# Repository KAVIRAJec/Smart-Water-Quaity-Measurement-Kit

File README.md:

# 🌐 Smart Water Quality Monitoring System Repository

Welcome to the repository for our Smart Water Quality Monitoring System! 🚰

## Project Overview

This repository hosts the code and documentation for an innovative smart water quality monitoring system. Our goal is to provide real-time insights into the quality of drinking water through a seamlessly integrated system.

## Key Components

- **Double-layer PCB Design:** Schematics and layouts meticulously crafted for enhanced performance.
  
- **3D-Printed Sensor Housings:** Custom-designed sensor housings using advanced 3D printing techniques.
  
- **Industrial Sensors:** Integration of industrial-grade pH, ORP, TDS, and turbidity sensors for accurate readings.

- **Raspberry Pi 4:** The core of our system, handling data processing and communication tasks efficiently.

- **Nextion HMI Touch Display:** An interactive touch display for real-time data visualization.

- **Mobile Application:** Developed using React Native, Node.js Express, and a robust database for accessible monitoring.

## Contributions

- **PCB Design:** Developed intricate double-layer PCB schematics and layouts.
  
- **3D Design and Printing:** Created and printed custom sensor housings for optimal functionality.
  
- **Hardware Integration:** Seamlessly integrated various hardware components and peripherals.
  
- **Raspberry Pi Programming:** Wrote the necessary code for Raspberry Pi, ensuring smooth data processing and communication.
  
- **Mobile Application Development:** Utilized React Native, Node.js Express, and database technologies for a user-friendly mobile application.

## Skills and Technologies Showcased

- **PCB Design:** Proficiency in crafting intricate PCB schematics and layouts.
  
- **3D Design and Printing:** Skillful creation and printing of custom 3D sensor housings.
  
- **Hardware Integration:** Expertise in integrating diverse hardware components seamlessly.
  
- **Raspberry Pi Programming:** Coding proficiency for efficient data processing on Raspberry Pi.
  
- **React Native:** Development of a mobile application for versatile accessibility.
  
- **Node.js Express:** Utilized for the backend of the mobile application.
  
- **Database Technologies:** Implemented a robust database for storing and managing data.

## License

This project is licensed under the MIT License
## Collaboration

This project is open to all collaborators! Feel free to contribute by forking the repository and creating pull requests.

## Documentation

Check the folders for comprehensive documentation related to the Smart Water Quality Monitoring System.

Feel free to explore the codebase and documentation to understand the inner workings of our Smart Water Quality Monitoring System! 💻🚀

#WaterQuality #SmartMonitoring #OpenSource #TechInnovation

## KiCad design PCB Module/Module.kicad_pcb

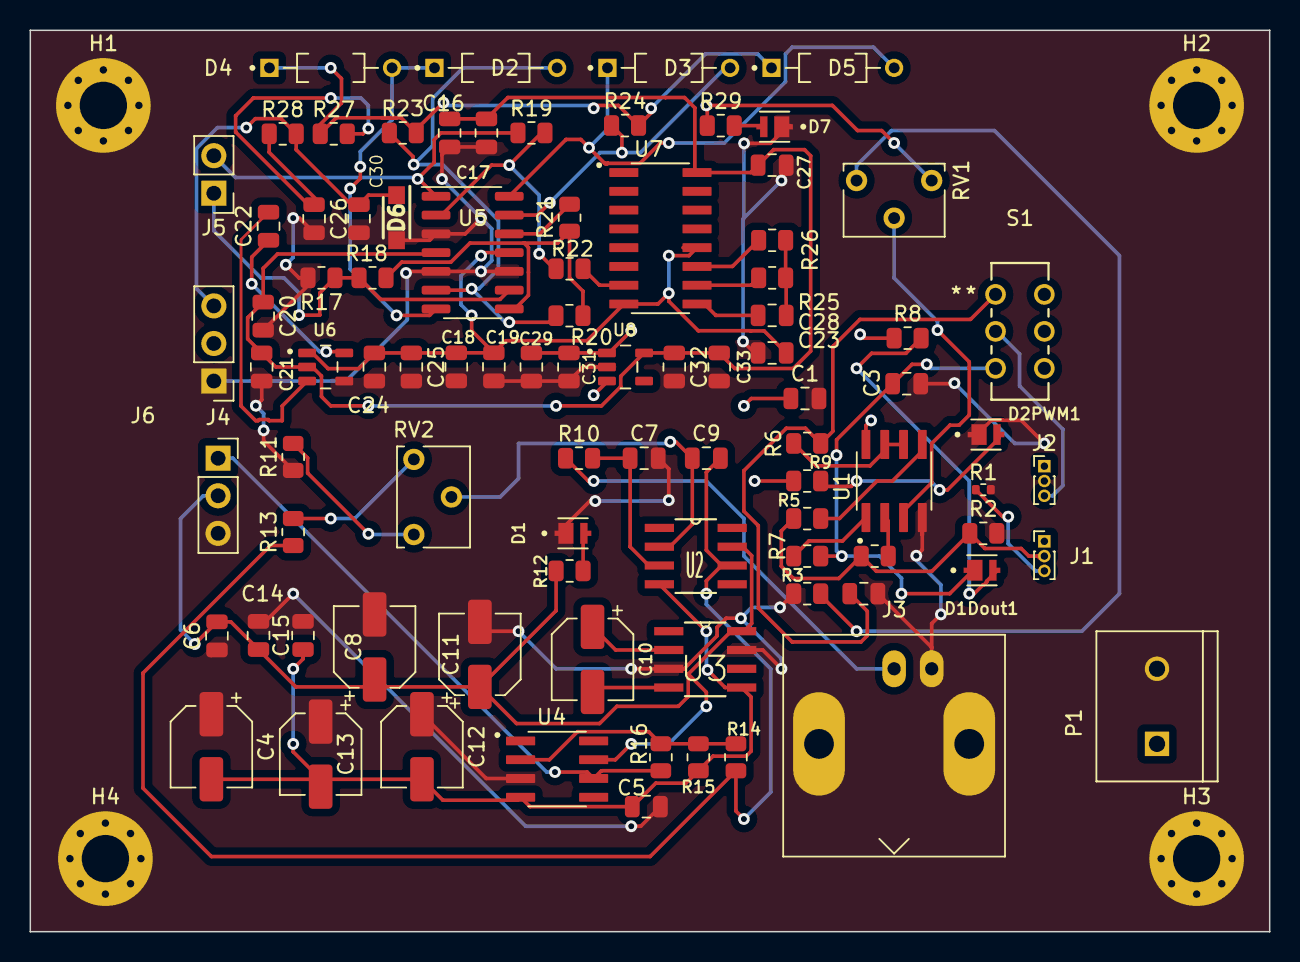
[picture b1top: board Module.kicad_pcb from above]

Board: 2 copper layers, 83.8 x 61.0 mm, 93 parts (0 on the bottom side), 50 nets.

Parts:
C1, C20, C22, C24, C29, C32: 10uF; C_0805_2012Metric
C2, C3, C5, C6, C14, C15, C17, C19, C21, C25, C27, C28, C31, C33: 100nF; C_0805_2012Metric
C4, C8, C11, C13: 10uF; CP_Elec_5x3
C7: 2.2nF; C_0805_2012Metric
C9, C26, C30: 1uF; C_0805_2012Metric
C10, C12: 100uF; CP_Elec_5x3
C16, C18: 4.7uF; C_0805_2012Metric
C23: 1nF; C_0805_2012Metric
D1, D1Dout1, D2PWM1, D7: MP-2016-1100-27-90; LED_MP-2016-1100-27-90
D2, D3, D4, D5: 1N4148; DIOAD829W49L456D191
D6: 1N5819W; SODFL3618X110N
H1, H2, H3, H4: MountingHole_Pad; MountingHole_3.2mm_M3_Pad_Via
J1, J2: Conn_01x03_Pin; PinHeader_1x03_P1.00mm_Vertical
J3: Conn_Coaxial; BNC_Amphenol_B6252HB-NPP3G-50_Horizontal
J4: Conn_01x03_Pin; PinSocket_1x03_P2.54mm_Vertical
J5: Conn_01x02_Pin; PinHeader_1x02_P2.54mm_Vertical
J6: Conn_01x03_Pin; PinHeader_1x03_P2.54mm_Vertical
P1: 282837-2; TE_282837-2
R1: 500R; R_0402_1005Metric
R2: 4.7K; R_0805_2012Metric
R3: 22R; R_0805_2012Metric
R4, R5: 10K; R_0805_2012Metric
R6, R8, R9, R12: 1K; R_0805_2012Metric
R7: 100R; R_0805_2012Metric
R10: 4.7M; R_0805_2012Metric
R11: 1k; R_0805_2012Metric
R13: 2.2K; R_0805_2012Metric
R14, R16: 30K; R_0805_2012Metric
R15: 75K; R_0805_2012Metric
R17: 1M-1%; R_0805_2012Metric
R18, R29: 5.6K-1%; R_0805_2012Metric
R19: 6.8K-1%; R_0805_2012Metric
R20, R21, R23, R24, R25, R27, R28: 10K-1%; R_0805_2012Metric
R22, R26: 100K-1%; R_0805_2012Metric
RV1: 10K; Potentiometer_Vishay_T73XX_Horizontal
RV2: 5K; Potentiometer_Vishay_T73XX_Horizontal
S1: JS202011CQN; SWITCH_011CQN
U1: LMV358IDR; SOIC127P599X175-8N
U2: CA3140AMZ; SOIC127P600X175-8N
U3: ADM8660ARZ; SOIC127P600X175-8N
U4: TL081BCDG4; SOIC127P599X175-8N
U5: LMV324; SOIC-14_3.9x8.7mm_P1.27mm
U6: TPS60400DBVR; SOT95P280X145-5N
U7: CD4060BM; SOIC127P600X175-16N
U8: TLV73330PDBVR; SOT95P280X145-5N

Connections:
+3.0V: C16.1, C17.1, C20.1, C21.1, C27.1, C32.1, C33.1, U5.4 (V+), U6.2 (IN), U7.16 (VCC), U8.5 (OUT)
+5V: C6.2, C8.1, C11.1, C14.1, J4.2, R12.1, U2.7 (V+), U3.8 (V+), U4.7 (VCC+)
-3.0V: C18.1, C19.1, C24.1, C25.1, C28.2, U5.11 (V-), U6.1 (OUT), U7.8 (GND), U7.12 (RESET)
-5V: C4.2, C5.1, C12.2, C13.2, C15.1, R15.2, U2.4 (V-), U3.5 (OUT), U4.4 (VCC-)
/Dout: C3.1, D1Dout1.C, R7.2, S1.3
/sensor_out: J2.3, S1.2
GND: C1.2, C2.2, C3.2, C4.1, C5.2, C6.1, C7.2, C8.2, C11.2, C12.1, C13.1, C14.2, C15.2, C16.2, C17.2, C18.2, C19.2, C20.2, C21.2, C24.2, C25.2, C26.2, C27.2, C28.1, C29.2, C30.2, C31.2, C32.2, C33.2, D1.C, D2PWM1.C, D6.2 (A), D7.C, H1.1, H2.1, H3.1, H4.1, J2.2, J3.2 (Ext), J4.3, J6.1, P1.2, R1.2, R2.2, R3.1, R11.1, R17.2, U1.4 (V-), U3.3 (GND), U3.7 (SD), U4.3 (IN+), U5.3 (+), U5.5 (+), U5.10 (+), U6.4 (GND), U8.2 (GND)
unnamed: C2.1, R6.2, S1.1
unnamed: C23.1, R25.1, R26.1
unnamed: C26.1, R27.2, R28.1
unnamed: D1.A, R12.2
unnamed: D1Dout1.A, R8.2
unnamed: D2.C, D4.A, U5.7
unnamed: D2PWM1.A, R9.2
unnamed: D3.C, D5.A, U5.14
unnamed: D4.C, D5.C, R23.2, R24.2, R27.1
unnamed: C30.1, D6.1 (K), J6.3, R28.2
unnamed: D7.A, R29.2
unnamed: J1.2, R2.1, R4.1, R5.1
unnamed: J1.3, R1.1
unnamed: J3.1 (In), R10.1
unnamed: J4.1, R16.2, U4.6 (OUT)
unnamed: J5.1, R17.1, R18.1, U5.9 (-)
unnamed: J5.2, R19.1, U5.1
unnamed: R3.2, RV1.3
unnamed: R11.2, RV2.3
unnamed: R13.2, RV2.1
unnamed: R18.2, R20.1, R21.1, U5.8
unnamed: RV1.2, U1.3 (INA+)
unnamed: R4.2, U1.2 (INA-)
unnamed: R5.2, U1.5 (INB+)
unnamed: R6.1, U1.6 (INB-), U1.7 (OUT_B)
unnamed: R7.1, U1.1 (OUT_A)
unnamed: C9.1, RV2.2, U2.2 (INV._INPUT)
unnamed: C7.1, R10.2, U2.3 (NON-INV._INPUT)
unnamed: C9.2, R13.1, R14.1, U2.6 (OUTPUT)
unnamed: C10.1, U3.2 (CAP+)
unnamed: C10.2, U3.4 (CAP-)
unnamed: R14.2, R15.1, R16.1, U4.2 (IN-)
unnamed: R19.2, R22.1, U5.2 (-)
unnamed: D2.A, R20.2, R23.1, U5.6 (-)
unnamed: R21.2, U5.12 (+)
unnamed: D3.A, R24.1, U5.13 (-)
unnamed: C22.1, U6.5 (CFLY+)
unnamed: C22.2, U6.3 (CFLY-)
unnamed: C23.2, U7.9 (EN1)
unnamed: R25.2, U7.10 (EN2)
unnamed: R26.2, U7.11 (EN3)
unnamed: R22.2, U7.7 (Q4)
VCC: C1.1, C29.1, C31.1, J1.1, J2.1, J6.2, P1.1, R8.1, R9.1, R29.1, RV1.1, U1.8 (V+), U8.1 (IN), U8.3 (EN)

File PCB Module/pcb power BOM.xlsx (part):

BILL OF MATERIAL
Item | Quantity | Reference | Value | PART TYPE | PCB Footprint | Manufacturer Part Number | Manfacturer Name | Description
1.0 | 1.0 | C1 | 10uF | CAP | C_0805_2012Metric | CL21A106KOCLRNC | Samsung Electro-Mechanics | 10 µF ±10% 16V Ceramic Capacitor X5R 0805 (2012 Metric)(3.4mm*1.96mm)
2.0 | 1.0 | C4 | 10uF | Polarized CAP | CP_Elec_5x3 | EDK106M035A9BAA | KEMET | 10 µF 35 V Aluminum Electrolytic Capacitors Radial, Can - SMD 2000 Hrs @ 85°C(7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
3.0 | 1.0 | C8 | 10uF | Polarized CAP | CP_Elec_5x3 | EDK106M035A9BAA | KEMET | 10 µF 35 V Aluminum Electrolytic Capacitors Radial, Can - SMD 2000 Hrs @ 85°C(7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
4.0 | 1.0 | C9 | 1uF | CAP | C_0805_2012Metric | CL21B105KAFNNNE | Samsung Electro-Mechanics | 1 µF ±10% 25V Ceramic Capacitor X7R 0805 (2012 Metric)(3.6mm*1.96mm)
5.0 | 1.0 | C10 | 100uF | Polaroid CAP | CP_Elec_5x3 | EDK107M035A9HAA | KEMET | 100 µF 35 V Aluminum Electrolytic Capacitors Radial, Can - SMD 2000 Hrs @ 85°C(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
6.0 | 1.0 | C11 | 10uF | Polarized CAP | CP_Elec_5x3 | EDK106M035A9BAA | KEMET | 10 µF 35 V Aluminum Electrolytic Capacitors Radial, Can - SMD 2000 Hrs @ 85°C(7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
7.0 | 1.0 | C12 | 100uF | Polarized CAP | CP_Elec_5x3 | EDK107M035A9HAA | KEMET | 100 µF 35 V Aluminum Electrolytic Capacitors Radial, Can - SMD 2000 Hrs @ 85°C(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
8.0 | 1.0 | C13 | 10uF | Polarized CAP | CP_Elec_5x3 | EDK106M035A9BAA | KEMET | 10 µF 35 V Aluminum Electrolytic Capacitors Radial, Can - SMD 2000 Hrs @ 85°C(7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
9.0 | 1.0 | C16 | 4.7uF | CAP | C_0805_2012Metric | CL21A475KAQNNNE | Samsung Electro-Mechanics | 4.7 µF ±10% 25V Ceramic Capacitor X5R 0805 (2012 Metric)(3.4mm*1.96mm)
10.0 | 1.0 | C18 | 4.7uF | CAP | C_0805_2012Metric | CL21A475KAQNNNE | Samsung Electro-Mechanics | 4.7 µF ±10% 25V Ceramic Capacitor X5R 0805 (2012 Metric)(3.4mm*1.96mm)
11.0 | 1.0 | C20 | 10uF | CAP | C_0805_2012Metric | CL21A106KOCLRNC | Samsung Electro-Mechanics | 10 µF ±10% 16V Ceramic Capacitor X5R 0805 (2012 Metric)(3.4mm*1.96mm)
12.0 | 1.0 | C22 | 10uF | CAP | C_0805_2012Metric | CL21A106KOCLRNC | Samsung Electro-Mechanics | 10 µF ±10% 16V Ceramic Capacitor X5R 0805 (2012 Metric)(3.4mm*1.96mm)
13.0 | 1.0 | C24 | 10uF | CAP | C_0805_2012Metric | CL21A106KOCLRNC | Samsung Electro-Mechanics | 10 µF ±10% 16V Ceramic Capacitor X5R 0805 (2012 Metric)(3.4mm*1.96mm)
14.0 | 1.0 | C26 | 1uF | CAP | C_0805_2012Metric | CL21B105KAFNNNE | Samsung Electro-Mechanics | 1 µF ±10% 25V Ceramic Capacitor X7R 0805 (2012 Metric)(3.4mm*1.96mm)
15.0 | 1.0 | C29 | 10uF | CAP | C_0805_2012Metric | CL21A106KOCLRNC | Samsung Electro-Mechanics | 10 µF ±10% 16V Ceramic Capacitor X5R 0805 (2012 Metric)(3.4mm*1.96mm)
16.0 | 1.0 | C30 | 1uF | CAP | C_0805_2012Metric | CL21B105KAFNNNE | Samsung Electro-Mechanics | 1 µF ±10% 25V Ceramic Capacitor X7R 0805 (2012 Metric)(3.4mm*1.96mm)
17.0 | 1.0 | C32 | 10uF | CAP | C_0805_2012Metric | CL21A106KOCLRNC | Samsung Electro-Mechanics | 10 µF ±10% 16V Ceramic Capacitor X5R 0805 (2012 Metric)(3.4mm*1.96mm)
18.0 | 1.0 | R1 | 500R | RES | Resistor_SMD:R_0402_2012Metric | PNM0402E5000BST1 | Vishay Dale Thin Film | 500 Ohms ±0.1% 0.05W, 1/20W Chip Resistor 0402 (1005 Metric) Anti-Sulfur, Moist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
19.0 | 1.0 | R2 | 4.7K | RES | Resistor_SMD:R_0805_2012Metric | RC0805JR-074K7L | YAGEO | 4.7 kOhms ±5% 0.125W, 1/8W Chip Resistor 0805 (2012 Metric) Moisture Resistant 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
20.0 | 1.0 | R3 | 22 ohm | RES | Resistor_SMD:R_0805_2012Metric | RC0805JR-0722RL | YAGEO | 22 Ohms ±5% 0.125W, 1/8W Chip Resistor 0805 (2012 Metric) Moisture Resistant Th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
21.0 | 1.0 | R4 | 10K | RES | Resistor_SMD:R_0805_2012Metric | RC0805JR-0710KL | YAGEO | 10 kOhms ±5% 0.125W, 1/8W Chip Resistor 0805 (2012 Metric) Moisture Resistant T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
22.0 | 1.0 | R5 | 10K | RES | Resistor_SMD:R_0805_2012Metric | RC0805JR-0710KL | YAGEO | 10 kOhms ±5% 0.125W, 1/8W Chip Resistor 0805 (2012 Metric) Moisture Resistant T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
23.0 | 1.0 | R6 | 1K | RES | Resistor_SMD:R_0805_2012Metric | RNCP0805FTD1K00 | Stackpole Electronics Inc | 1 kOhms ±1% 0.25W, 1/4W Chip Resistor 0805 (2012 Metric) Anti-Sulfur Thin Film(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
24.0 | 1.0 | R7 | 100R | RES | Resistor_SMD:R_0805_2012Metric | RN73C2A100RBTDF | TE Connectivity Passive Product | 100 Ohms ±0.1% 0.1W, 1/10W Chip Resistor 0805 (2012 Metric) Thin Film(3.36mm*1.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
25.0 | 1.0 | R8 | 1K | RES | Resistor_SMD:R_0805_2012Metric | RNCP0805FTD1K00 | Stackpole Electronics Inc | 1 kOhms ±1% 0.25W, 1/4W Chip Resistor 0805 (2012 Metric) Anti-Sulfur Thin Film(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
26.0 | 1.0 | R9 | 1K | RES | Resistor_SMD:R_0805_2012Metric | RNCP0805FTD1K00 | Stackpole Electronics Inc | 1 kOhms ±1% 0.25W, 1/4W Chip Resistor 0805 (2012 Metric) Anti-Sulfur Thin Film(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
27.0 | 1.0 | R10 | 4.7M | RES | Resistor_SMD:R_0805_2012Metric | RC0805JR-074M7L | YAGEO | 4.7 MOhms ±5% 0.125W, 1/8W Chip Resistor 0805 (2012 Metric) Moisture Resistant 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
28.0 | 1.0 | R11 | 1K | RES | Resistor_SMD:R_0805_2012Metric | RNCP0805FTD1K00 | Stackpole Electronics Inc | 1 kOhms ±1% 0.25W, 1/4W Chip Resistor 0805 (2012 Metric) Anti-Sulfur Thin Film(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
29.0 | 1.0 | R12 | 1K | RES | Resistor_SMD:R_0805_2012Metric | RNCP0805FTD1K00 | Stackpole Electronics Inc | 1 kOhms ±1% 0.25W, 1/4W Chip Resistor 0805 (2012 Metric) Anti-Sulfur Thin Film(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
30.0 | 1.0 | R13 | 2.2K | RES | Resistor_SMD:R_0805_2012Metric | RC0805JR-072K2L | YAGEO | 2.2 kOhms ±5% 0.125W, 1/8W Chip Resistor 0805 (2012 Metric) Moisture Resistant 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
31.0 | 1.0 | R14 | 30K | RES | Resistor_SMD:R_0805_2012Metric | RC0805JR-0730KL | YAGEO | 30 kOhms ±5% 0.125W, 1/8W Chip Resistor 0805 (2012 Metric) Moisture Resistant T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
32.0 | 1.0 | R15 | 75K | RES | Resistor_SMD:R_0805_2012Metric | RC0805JR-0775KL | YAGEO | 75 kOhms ±5% 0.125W, 1/8W Chip Resistor 0805 (2012 Metric) Moisture Resistant T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
33.0 | 1.0 | R16 | 30K | RES | Resistor_SMD:R_0805_2012Metric | RC0805JR-0730KL | YAGEO | 30 kOhms ±5% 0.125W, 1/8W Chip Resistor 0805 (2012 Metric) Moisture Resistant T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
34.0 | 1.0 | R17 | 1M-1% | RES-1%Tolerence | Resistor_SMD:R_0805_2012Metric | CRG0805F1M0 | TE Connectivity Passive Product | 1 MOhms ±1% 0.125W, 1/8W Chip Resistor 0805 (2012 Metric) Thick Film(3.36mm*1.9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
35.0 | 1.0 | R18 | 5.6K-1% | RES-1%Tolerence | Resistor_SMD:R_0805_2012Metric | RMCF0805FT5K60 | Stackpole Electronics Inc | 5.6 kOhms ±1% 0.125W, 1/8W Chip Resistor 0805 (2012 Metric) Automotive AEC-Q200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
36.0 | 1.0 | R19 | 6.8K-1% | RES-1%Tolerence | Resistor_SMD:R_0805_2012Metric | RMCF0805FT6K80 | Stackpole Electronics Inc | 6.8 kOhms ±1% 0.125W, 1/8W Chip Resistor 0805 (2012 Metric) Automotive AEC-Q200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
37.0 | 1.0 | R20 | 10K-1% | RES-1%Tolerence | Resistor_SMD:R_0805_2012Metric | RMCF0805FT10K0 | Stackpole Electronics Inc | 10 kOhms ±1% 0.125W, 1/8W Chip Resistor 0805 (2012 Metric) Automotive AEC-Q200 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
38.0 | 1.0 | R21 | 10K-1% | RES-1%Tolerence | Resistor_SMD:R_0805_2012Metric | RMCF0805FT10K0 | Stackpole Electronics Inc | 10 kOhms ±1% 0.125W, 1/8W Chip Resistor 0805 (2012 Metric) Automotive AEC-Q200 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
39.0 | 1.0 | R22 | 100K-1% | RES-1%Tolerence | Resistor_SMD:R_0805_2012Metric | RMCF0805FT100K | Stackpole Electronics Inc | 100 kOhms ±1% 0.125W, 1/8W Chip Resistor 0805 (2012 Metric) Automotive AEC-Q200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
40.0 | 1.0 | R23 | 10K-1% | RES-1%Tolerence | Resistor_SMD:R_0805_2012Metric | RMCF0805FT10K0 | Stackpole Electronics Inc | 10 kOhms ±1% 0.125W, 1/8W Chip Resistor 0805 (2012 Metric) Automotive AEC-Q200 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
41.0 | 1.0 | R24 | 10K-1% | RES-1%Tolerence | Resistor_SMD:R_0805_2012Metric | RMCF0805FT10K0 | Stackpole Electronics Inc | 10 kOhms ±1% 0.125W, 1/8W Chip Resistor 0805 (2012 Metric) Automotive AEC-Q200 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
42.0 | 1.0 | R25 | 10K-1% | RES-1%Tolerence | Resistor_SMD:R_0805_2012Metric | RMCF0805FT10K0 | Stackpole Electronics Inc | 10 kOhms ±1% 0.125W, 1/8W Chip Resistor 0805 (2012 Metric) Automotive AEC-Q200 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
43.0 | 1.0 | R26 | 100K-1% | RES-1%Tolerence | Resistor_SMD:R_0805_2012Metric | RMCF0805FT100K | Stackpole Electronics Inc | 100 kOhms ±1% 0.125W, 1/8W Chip Resistor 0805 (2012 Metric) Automotive AEC-Q200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

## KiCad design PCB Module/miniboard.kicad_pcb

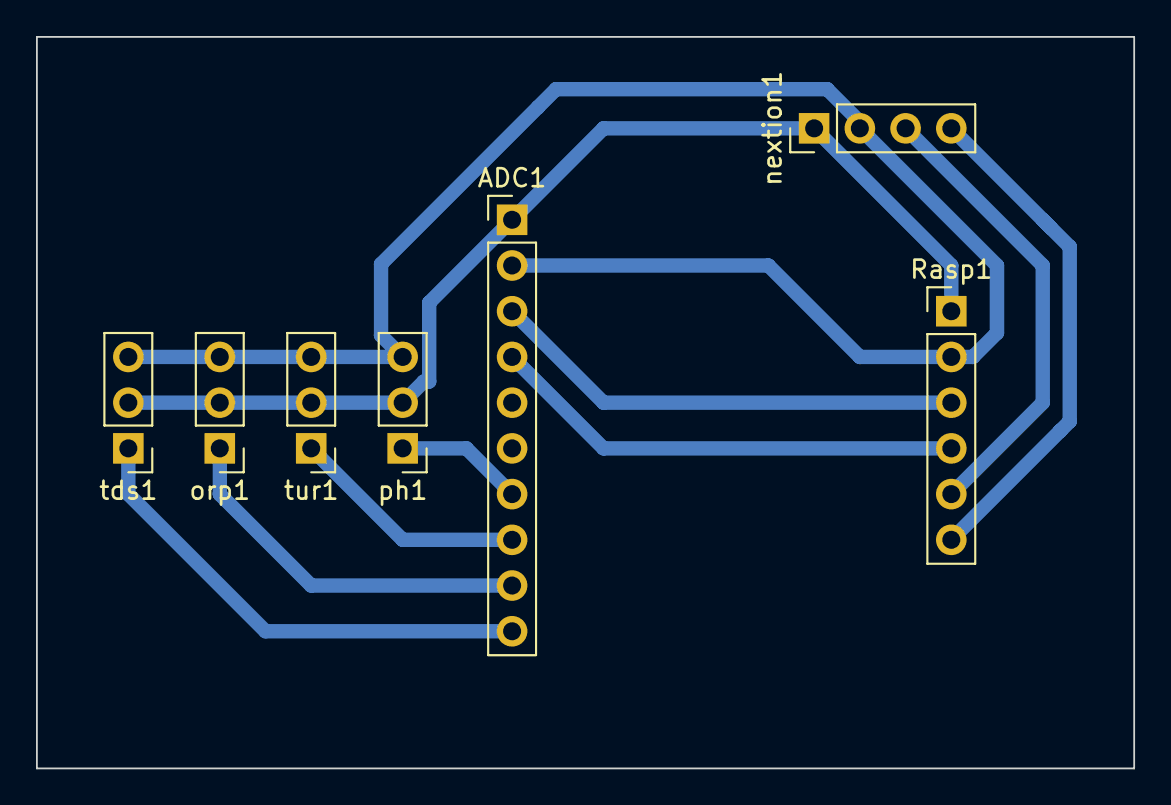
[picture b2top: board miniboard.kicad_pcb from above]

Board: 2 copper layers, 61.0 x 40.6 mm, 7 parts (0 on the bottom side), 10 nets.

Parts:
ADC1: Conn_01x10_Pin; PinHeader_1x10_P2.54mm_Vertical
Rasp1: Conn_01x06_Pin; PinHeader_1x06_P2.54mm_Vertical
nextion1: Conn_01x04_Pin; PinHeader_1x04_P2.54mm_Vertical
orp1: Conn_01x03_Pin; PinHeader_1x03_P2.54mm_Vertical
ph1: Conn_01x03_Pin; PinHeader_1x03_P2.54mm_Vertical
tds1: Conn_01x03_Pin; PinHeader_1x03_P2.54mm_Vertical
tur1: Conn_01x03_Pin; PinHeader_1x03_P2.54mm_Vertical

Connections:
+5V: ADC1.1, Rasp1.1, nextion1.1, orp1.2, ph1.2, tds1.2, tur1.2
GND: ADC1.2, Rasp1.2, nextion1.2, orp1.3, ph1.3, tds1.3, tur1.3
unnamed: ADC1.3, Rasp1.3
unnamed: ADC1.4, Rasp1.4
unnamed: ADC1.7, ph1.1
unnamed: ADC1.8, tur1.1
unnamed: ADC1.9, orp1.1
unnamed: ADC1.10, tds1.1
unnamed: Rasp1.5, nextion1.3
unnamed: Rasp1.6, nextion1.4

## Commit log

2023-11-15 final commit
2023-11-15 Database reference
2023-11-16 Updated code.py
2023-11-16 updated at final evaluation
2024-07-21 Added High quality Camera Images
